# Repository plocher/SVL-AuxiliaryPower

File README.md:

# SVL-AuxiliaryPower
## License: CERN Open Hardware Licence v1.2

SVL Aux Power

Silicon Valley Lines' layout uses a dedicated power bus for all layout animations (street lighting, building lights, signs, sound modules...)

Think "simple 555 based circuits", flashing emergency vehicle lights, streetlights, "arduinos" and "grain of wheat/rice bulbs":
* 12v for motors/animation
* 9v for lights (derated from 12 to make them last longer)
* 5v for "logic" circuits
* 1.5v for structure lights
* DCC for accessory decoders

This device sits on the DCC Accssory bus (V3.0) or a dedicated 12VDC bus (V2.0) and provides
* 2x user adjustable switching supply outputs (1.3v - 30v @ 1A),
* a rectified/filtered 12-14vDC and
* A 1A fused DCC feed

The regulation is done by Buck Step-down LM2596 Power Converter Module DC 4.0~40 1.3-37V with LED voltage feedback
See http://www.ebay.com/itm/222245521575

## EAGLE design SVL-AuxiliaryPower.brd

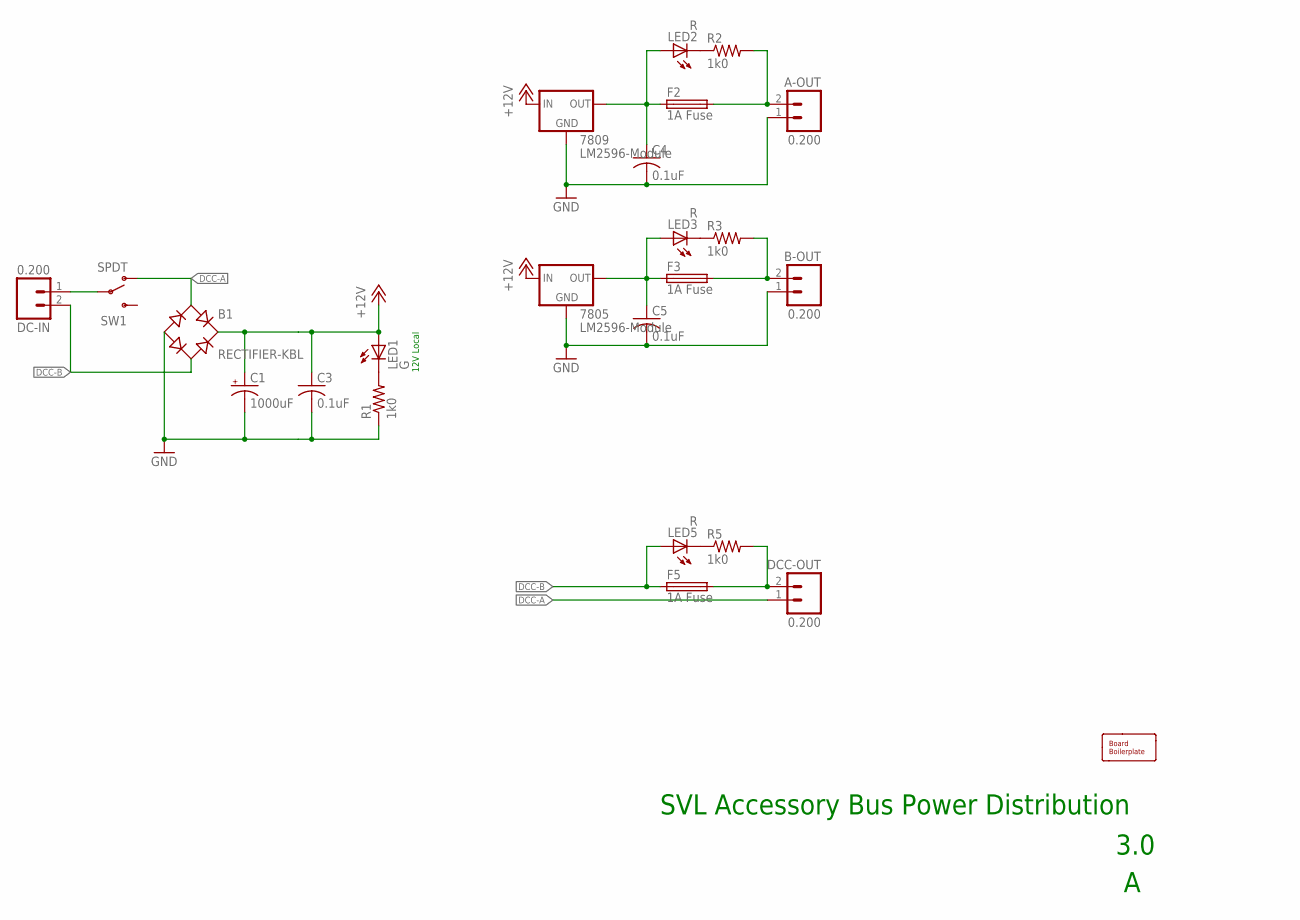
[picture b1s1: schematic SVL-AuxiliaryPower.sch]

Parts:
7805, 7809: LM2596-Module; LM2596-MODULE
A-OUT: 0.200; MSTB2
B1: RECTIFIER-KBL; KBL
B-OUT: 0.200; MSTB2
BOARD1: BOARD100X100; BOARD-SEEED10X10
C1: 1000uF; E5-10.5
C3, C4, C5: 0.1uF; C050-024X044
DC-IN: 0.200; MSTB2
DCC-OUT: 0.200; MSTB2
F2, F3, F5: 1A Fuse; POLYFUSE
LED1: G; LED5MM
LED2, LED3, LED5: R; LED5MM
R1, R2, R3, R5: 1k0; AXIAL-0.4-RES
SW1: SPDT; SWITCH-SPDT-508

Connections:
+12V: 7805.IN+@1 (IN), 7805.IN+@2 (IN), 7809.IN+@1 (IN), 7809.IN+@2 (IN), B1.+, C1.+, C3.1, LED1.A
DCC-A: B1.AC1, DCC-OUT.1, SW1.1 (O)
DCC-B: B1.AC2, DC-IN.2, F5.1, LED5.A
GND: 7805.GND@1 (GND), 7805.GND@2 (GND), 7805.GND@3 (GND), 7805.GND@4 (GND), 7809.GND@1 (GND), 7809.GND@2 (GND), 7809.GND@3 (GND), 7809.GND@4 (GND), A-OUT.1, B1.-, B-OUT.1, C1.-, C3.2, C4.2, C5.2, R1.P$1 (1)
unnamed: A-OUT.2, F2.2, R2.P$2 (2)
unnamed: B-OUT.2, F3.2, R3.P$2 (2)
unnamed: DCC-OUT.2, F5.2, R5.P$2 (2)
unnamed: 7809.OUT+@1 (OUT), 7809.OUT+@2 (OUT), C4.1, F2.1, LED2.A
unnamed: 7805.OUT+@1 (OUT), 7805.OUT+@2 (OUT), C5.1, F3.1, LED3.A
unnamed: LED2.K (C), R2.P$1 (1)
unnamed: LED3.K (C), R3.P$1 (1)
unnamed: LED1.K (C), R1.P$2 (2)
unnamed: LED5.K (C), R5.P$1 (1)
UNSWITCHED-DCC-A: DC-IN.1, SW1.2

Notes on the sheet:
12V Local
SVL Accessory Bus Power Distribution
3.0

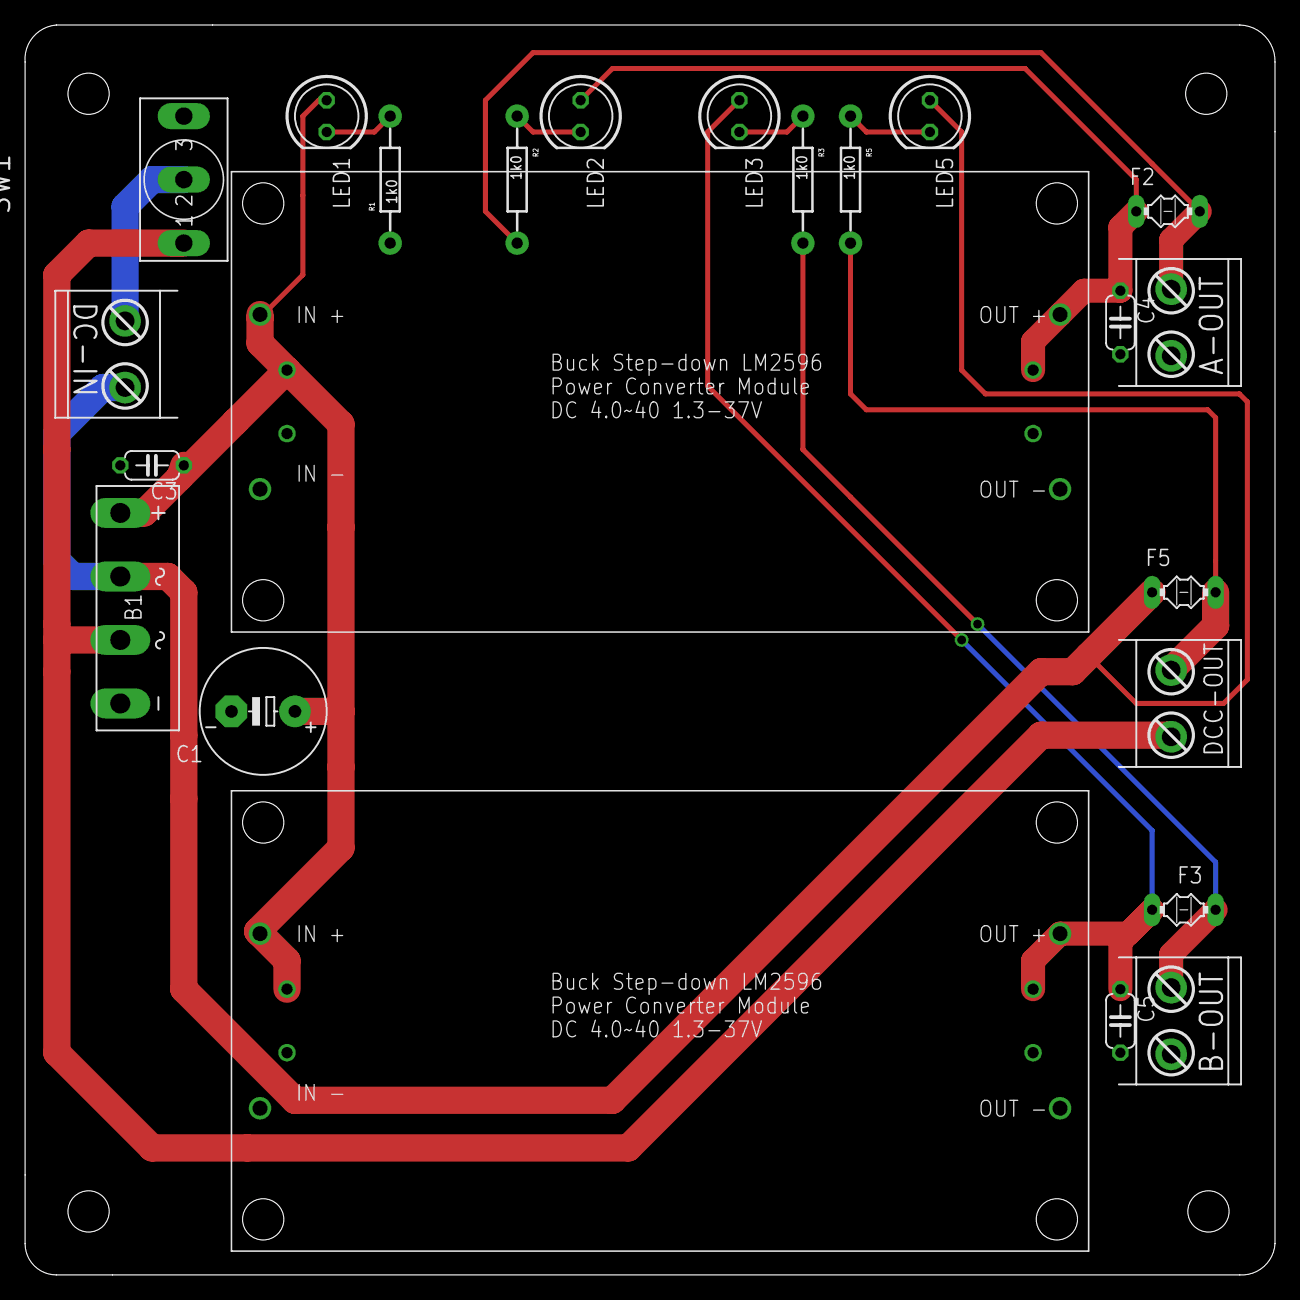
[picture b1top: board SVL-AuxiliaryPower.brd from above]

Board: 2 copper layers, 100.0 x 100.0 mm, 24 parts (0 on the bottom side), 14 nets.

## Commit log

2020-05-04 updated tags
2020-10-06 normalized values
